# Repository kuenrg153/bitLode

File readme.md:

## bitLode V2

bitLode V2 is an RP2040 USB adapter that connects a PC, laptop or Raspberry Pi to a Whatsminer M30 (and similar)
hashboard. It exposes the hashboard's UART, reset and I2C over USB.

It's a fork of [aditBoard v2](https://github.com/skot/aditBoard/tree/v2) by Skot. It changes the
board for Whatsminer hashboards and adds firmware, host tools and an AI diagnostics skill.

| Path | Contents |
|---|---|
| `bitLodeV2.kicad_pro` / `.kicad_sch` / `.kicad_pcb` | KiCad 10 project: schematic and 6-layer PCB |
| `bitLodeV2.kicad_sym`, `bitLodeV2.pretty/`, `bitLodeV2.3dshapes/` | project-local symbols, footprints and 3D models |
| `Manufacturing Files/` | Gerbers, drill files, BOM and component placement for PCBA (e.g. [JLCPCB](https://jlcpcb.com)) |
| [`firmware/`](firmware/) | RP2040 firmware source (Rust/Embassy) with prebuilt `bin/bitlode-fw.elf` and `bin/bitlode-fw.uf2` |
| [`tools/`](tools/) | Python host tools: port discovery, system commands, hashboard init/replay, nonce verification, rig power |
| [`skills/`](skills/) | AI agent skill for diagnosing a Whatsminer M30S (KF1950) hashboard through the bitLode |

### Quick start

1. **Hardware** Send `Manufacturing Files/gerbers/`, the BOM and the placement file to your PCB assembler. Some notes: 

a) Fab houses might try to replace the cyrstal with an oscillator (learned this the hard way) - don't let them!

b) The LED is hard to source - but it works fine with out it!

c) Just do SMT at the fab house - solder the connector yourself and save a little bit. You can even try to sample the connector for free from Samtec - SQT-107-01-L-D-RA

d) Note that this version interferes with the fan in the original enclosure. If you're looking to use it long term in the enclosure you probably want to modify it (make the board into a bit of an upside down L and extend the header down) to clear the fan.

e) Currently I have NOT made the AntHat (https://github.com/skot/AntHat) equivalent for controlling the Whatsminer PSU and fans. Let me know if there is interest there.

2. **Firmware** 
The firmware is based on https://github.com/256foundation/emberone-usbserial-fw with a few modifications around baud rates.

If you have trouble flashing it via the regular uf2 over boot loader then you can try using a Pi Pico running Debugprobe
https://www.electronics-lab.com/understanding-the-ways-to-debug-your-raspberry-pi-pico-development-board/

If you go this route then it's really handy to get an adapter ( https://www.aliexpress.com/item/1005009527726103.html ) to bring out the SWD lines.

To build it yourself, see [`firmware/README.md`](firmware/README.md).
   
3. **Plug in USB.** The board appears as `e3be:40e1` with two serial ports: control (interface 0) and ASIC UART (interface 2).
   ```sh
   pip install pyserial
   python3 tools/bitlode_sys.py ident   # -> ember-one kf1950 pio96 +sys-cmds 2026-09-15
   ```

### AI skill
The point of these skills is to help people learn how to communicate with, configure and diagnose Whatsminer M30 hashboards. 

I haven't yet done it but you could pair these skills up with Mujina (https://github.com/256foundation/mujina) and actually hash. Note that the RP2040 canNOT keep up with the 12Mbaud native baud rate required to fully hash but maybe someone can run with this project and figure that out.

`skills/bitlode-hashboard-diag/` is a [Claude Code skill](https://docs.claude.com/en/docs/claude-code/skills).
Link it into your skills directory, then run the agent from the repository root so its
relative paths (`tools/`, `sessions/`, `captures/`) resolve:

```sh
mkdir -p ~/.claude/skills
ln -s "$PWD/skills/bitlode-hashboard-diag" ~/.claude/skills/bitlode-hashboard-diag
```

Before its hashing test (T3), the skill needs:
- the job pool, generated once with `cd tools && python3 make_fresh_jobs.py 165000`
- the `whatsminer_private_api_py` package (its `wm_ssh.py`) for `tools/wm.sh`, pointed to by `WM_API_DIR`
- a known-good nonce capture for the verifier's control, pointed to by `KF_CONTROL_PKL`

### License

Firmware: GPL-3.0 (see `firmware/LICENSE`).

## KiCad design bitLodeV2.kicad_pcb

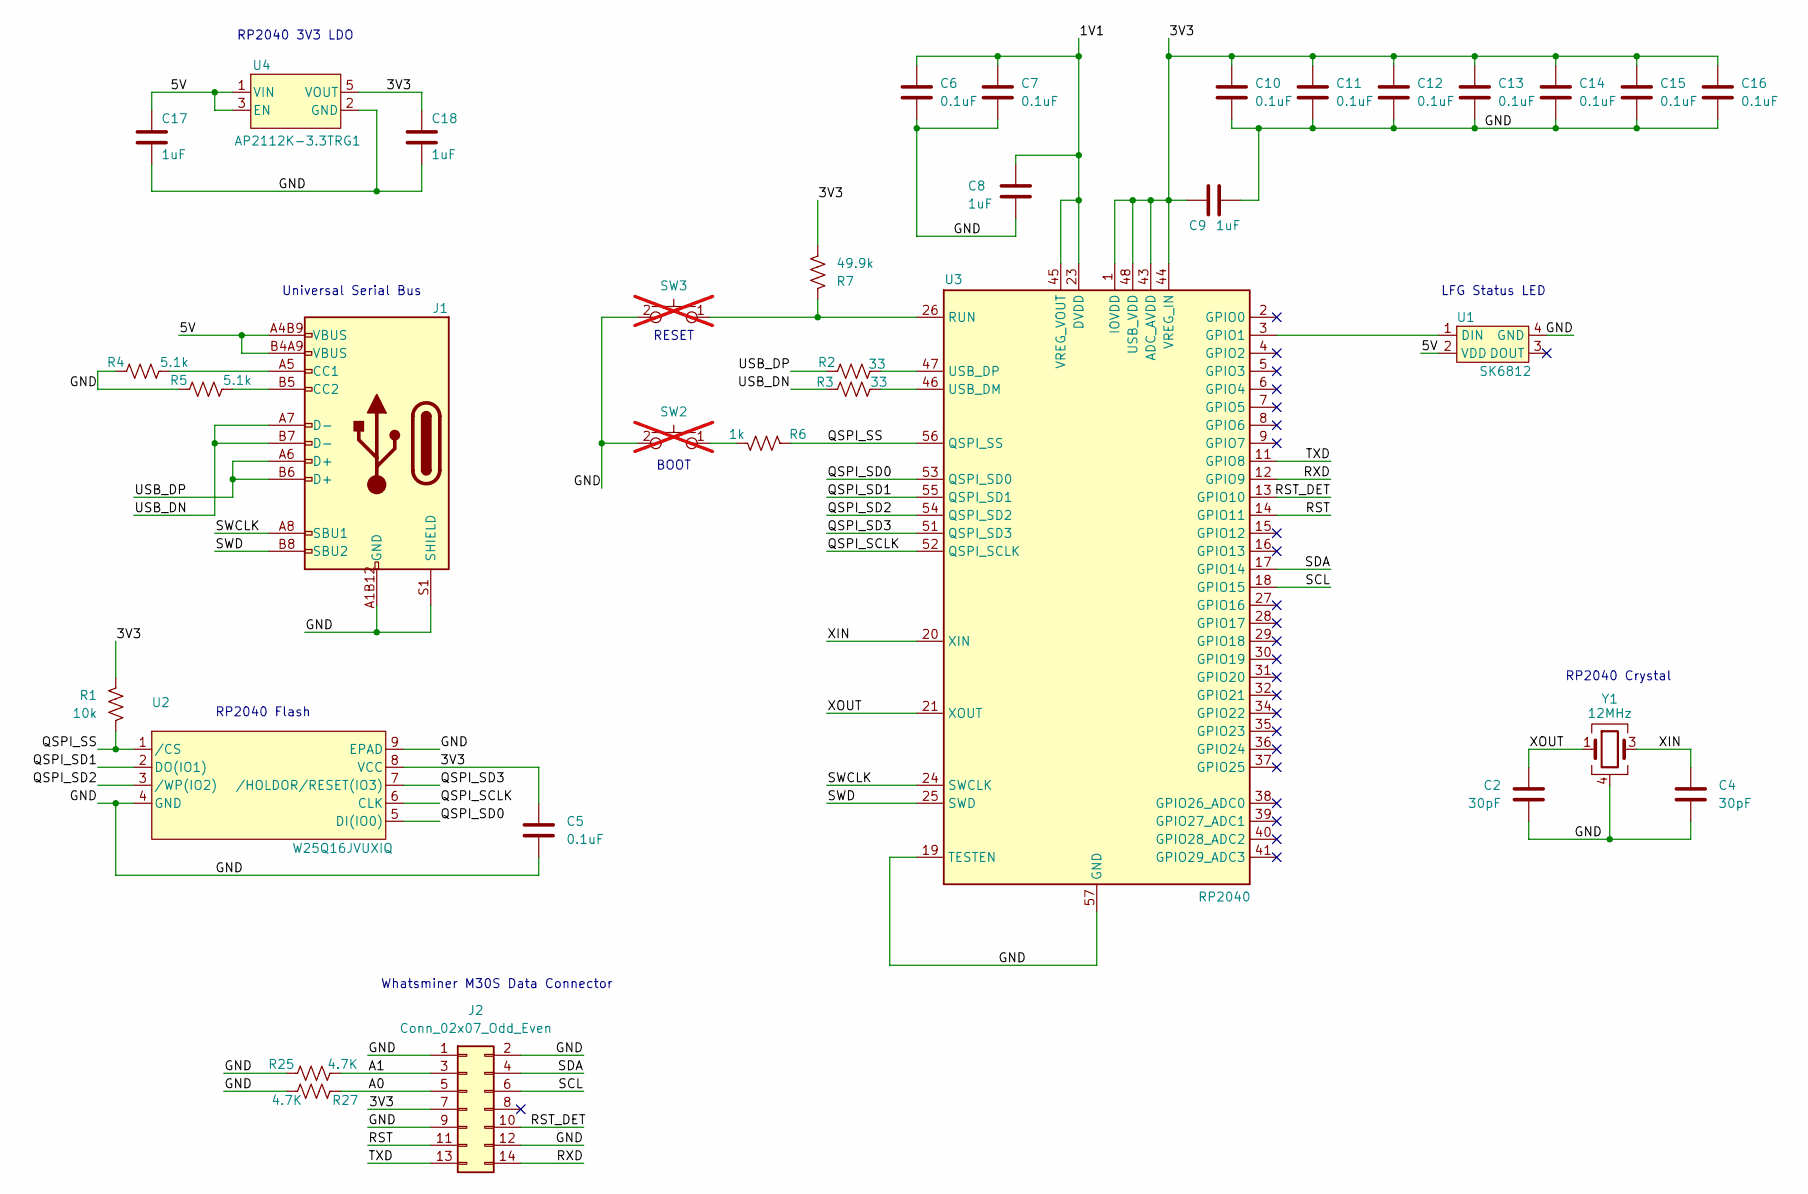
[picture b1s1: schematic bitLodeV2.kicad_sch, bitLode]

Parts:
C2, C4: 30pF; C_0402_1005Metric; PARTNO 0402CG300J500NT; JLC Part Basic Part
C5, C6, C7, C10, C11, C12, C13, C14, C15, C16: 0.1uF; C_0402_1005Metric; PARTNO CL05B104KB54PNC; JLC Part Basic Part
C8, C9: 1uF; C_0402_1005Metric; PARTNO CL05A105KA5NQNC; JLC Part Basic Part
C17, C18: 1uF; C_0402_1005Metric; PARTNO CL05A105KA5NQNC; LCSC C52923
J1: USB_C_Receptacle_USB2.0; USB_C_Receptacle_GCT_USB4105-xx-A_16P_TopMnt_Horizontal; PARTNO USB4105-GF-A; LCSC C2988369
J2: Conn_02x07_Odd_Even; PinSocket_2x07_P2.00mm_Horizontal
R1: 10k; R_0402_1005Metric; PARTNO 0402WGF1002TCE; LCSC C25744
R2, R3: 33; R_0402_1005Metric; PARTNO 0402WGF330JTCE; JLC Part Basic Part
R4, R5: 5.1k; R_0402_1005Metric; PARTNO RMCF0402JT5K10; LCSC C25905
R6: 1k; R_0402_1005Metric; PARTNO RC0402FR-071KL; LCSC C106235
R7: 49.9k; R_0402_1005Metric; PARTNO RC0402FR-0749K9L; LCSC C137969
R25, R27: 4.7K; R_0402_1005Metric; PARTNO RC0805FR-074K7L; LCSC Part C25900
SW2, SW3: GT-TC029B-H025-L1N; SW_CS1213AGF260_CRS; PARTNO CS1213AGF260; LCSC C5578986; not fitted
U1: SK6812; LED-SMD_4P-L4.0-W1.6-L; PARTNO SK6812SIDE-A-RVS; LCSC C2890037
U2: W25Q16JVUXIQ; USON8_L2.0-W3.0-P0.50-BL-EP; PARTNO W25Q16JVUXIQ; LCSC C2843335
U3: RP2040; QFN-56-1EP_7x7mm_P0.4mm_EP3.2x3.2mm; PARTNO RP2040; LCSC C2040
U4: AP2112K-3.3TRG1; SOT-25-5_L2.9-W1.6-P0.95-LS2.8-BL; PARTNO AP2112K-3.3TRG1; LCSC C51118
Y1: 12MHz; OSC-SMD_4P-L3.2-W2.5-BL; PARTNO X322512MSB4SI; LCSC C9002

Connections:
/1V1: C6.2, C7.2, C8.2, U3.23 (DVDD), U3.45 (VREG_VOUT), U3.50 (DVDD)
/3V3: C5.2, C9.1, C10.2, C11.2, C12.2, C13.2, C14.2, C15.2, C16.2, C18.1, J2.7, R1.1, R7.2, U2.8 (VCC), U3.1 (IOVDD), U3.10 (IOVDD), U3.22 (IOVDD), U3.33 (IOVDD), U3.42 (IOVDD), U3.43 (ADC_AVDD), U3.44 (VREG_IN), U3.48 (USB_VDD), U3.49 (IOVDD), U4.5 (VOUT)
/5V: C17.1, J1.A4B9 (VBUS), J1.B4A9 (VBUS), U1.2 (VDD), U4.1 (VIN), U4.3 (EN)
/A0: J2.5, R27.1
/A1: J2.3, R25.2
/GND: C2.1, C4.1, C5.1, C6.1, C7.1, C8.1, C9.2, C10.1, C11.1, C12.1, C13.1, C14.1, C15.1, C16.1, C17.2, C18.2, J1.A1B12 (GND), J1.B1A12 (GND), J1.S1 (SHIELD), J2.1, J2.2, J2.9, J2.12, R4.1, R5.1, R25.1, R27.2, SW2.2, SW3.2, U1.4 (GND), U2.4 (GND), U2.9 (EPAD), U3.19 (TESTEN), U3.57 (GND), U4.2 (GND), Y1.2, Y1.4
/QSPI_SCLK: U2.6 (CLK), U3.52 (QSPI_SCLK)
/QSPI_SD0: U2.5 (DI(IO0)), U3.53 (QSPI_SD0)
/QSPI_SD1: U2.2 (DO(IO1)), U3.55 (QSPI_SD1)
/QSPI_SD2: U2.3 (/WP(IO2)), U3.54 (QSPI_SD2)
/QSPI_SD3: U2.7 (/HOLDOR/RESET(IO3)), U3.51 (QSPI_SD3)
/QSPI_SS: R1.2, R6.1, U2.1 (/CS), U3.56 (QSPI_SS)
/RST: J2.11, U3.14 (GPIO11)
/RST_DET: J2.10, U3.13 (GPIO10)
/RXD: J2.14, U3.12 (GPIO9)
/SCL: J2.6, U3.18 (GPIO15)
/SDA: J2.4, U3.17 (GPIO14)
/SWCLK: J1.A8 (SBU1), U3.24 (SWCLK)
/SWD: J1.B8 (SBU2), U3.25 (SWD)
/TXD: J2.13, U3.11 (GPIO8)
/USB_DN: J1.A7 (D-), J1.B7 (D-), R3.1
/USB_DP: J1.A6 (D+), J1.B6 (D+), R2.1
/XIN: C4.2, U3.20 (XIN), Y1.3
/XOUT: C2.2, U3.21 (XOUT), Y1.1
unnamed: J1.A5 (CC1), R4.2
unnamed: J1.B5 (CC2), R5.2
unnamed: R6.2, SW2.1
unnamed: U1.1 (DIN), U3.3 (GPIO1)
unnamed: R7.1, SW3.1, U3.26 (RUN)
unnamed: R3.2, U3.46 (USB_DM)
unnamed: R2.2, U3.47 (USB_DP)

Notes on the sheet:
Whatsminer M30S Data Connector
LFG Status LED
RESET
RP2040 Flash
RP2040 Crystal
RP2040 3V3 LDO
BOOT
Universal Serial Bus

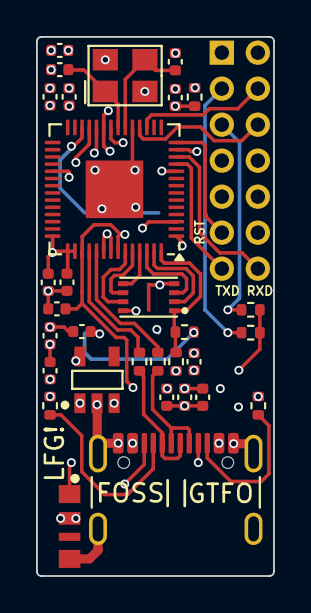
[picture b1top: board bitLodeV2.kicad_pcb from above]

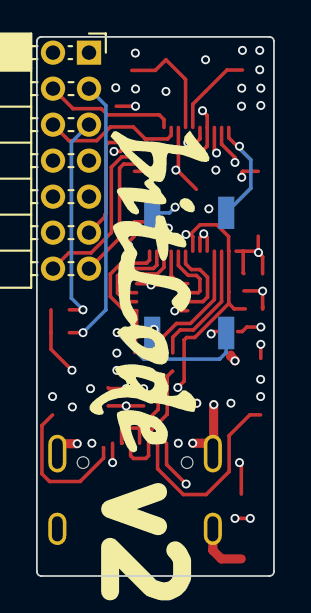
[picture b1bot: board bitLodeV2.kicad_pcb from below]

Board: 6 copper layers, 13.2 x 30.0 mm, 34 parts (3 on the bottom side), 31 nets.

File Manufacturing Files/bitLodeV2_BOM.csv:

"Id";"Designator";"Footprint";"Quantity";"Designation";"Supplier and ref";
1;"C2, C4";"C_0402_1005Metric";2;"30pF";;;
2;"C5, C6, C7, C10, C11, C12, C13, C14, C15, C16";"C_0402_1005Metric";10;"0.1uF";;;
3;"C8, C9, C17, C18";"C_0402_1005Metric";4;"1uF";;;
4;"J1";"USB_C_Receptacle_GCT_USB4105-xx-A_16P_TopMnt_Horizontal";1;"USB_C_Receptacle_USB2.0";;;
5;"J2";"PinSocket_2x07_P2.00mm_Horizontal";1;"Conn_02x07_Odd_Even";;;
6;"R1";"R_0402_1005Metric";1;"10k";;;
7;"R2, R3";"R_0402_1005Metric";2;"33";;;
8;"R4, R5";"R_0402_1005Metric";2;"5.1k";;;
9;"R6";"R_0402_1005Metric";1;"1k";;;
10;"R7";"R_0402_1005Metric";1;"49.9k";;;
11;"R25, R27";"R_0402_1005Metric";2;"4.7K";;;
12;"U1";"LED-SMD_4P-L4.0-W1.6-L";1;"SK6812";;;
13;"U2";"USON8_L2.0-W3.0-P0.50-BL-EP";1;"W25Q16JVUXIQ";;;
14;"U3";"QFN-56-1EP_7x7mm_P0.4mm_EP3.2x3.2mm";1;"RP2040";;;
15;"U4";"SOT-25-5_L2.9-W1.6-P0.95-LS2.8-BL";1;"AP2112K-3.3TRG1";;;
16;"Y1";"OSC-SMD_4P-L3.2-W2.5-BL";1;"12MHz";;;

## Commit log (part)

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2025-12-17 First push of bitLoad interface board
    Changes from Aditboard v2
    - move to 7x2mm connector and changed connections appropriately
    - changed logo on bottom silk to bitLode :)
2026-01-18 Fixed the Orientation
